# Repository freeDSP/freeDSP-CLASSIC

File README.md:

# freeDSP CLASSIC

BOARD STATUS: READY TO BE BUILT

MAIN COORDINATOR: [sudlud](https://github.com/sudlud)

The freeDSP CLASSIC is a cost-effective real-time audio signal processing solution for researchers and the do-it-yourself community. It is a bare circuit board that can be incorporated into your own projects. It comes with no housing. Easy assembling and simple programmability are the main focus. It is based on Analog Devices’ ADAU1701 DSP chip together with the free graphical development environment SigmaStudio. The programming model is function-block based – comparable to other graphical programming languages like PureData or Max/MSP. Many prebuilt blocks (e.g., filters, compressors, effects, or logic) can be placed in the signal path via drag and drop. If the included libraries do not have the functions needed, low-level blocks, such as multipliers and delays, can be wired together to create custom algorithms.

This board uses MAINLY THT components. The trickiest part is soldering the DSP, which comes in an SMD packaging. A complete SMD version is under development.

## Features

The freeDSP CLASSIC board offers two analog inputs and four analog outputs. Compared to other DSP solutions with easy programmability, the freeDSP and SigmaStudio offer a much wider range of DSP processing options and interface controls. It can be used in various audio applications, e.g.:

* Room compensation / system equalization
* Digital crossovers in active loudspeaker concepts
* Multiband dynamics processing
* Delay compensation / phase shift
* Bass enhancement
* Subwoofer integration
* Advanced instrument audio effect units
* Stereo image widening
…

For more information, please refer to the website www.freeDSP.cc and the documentation.  

## License

This work and all other materials under https://github.com/freeDSP are licensed under a <a rel="license" href="http://creativecommons.org/licenses/by-sa/4.0/legalcode">Creative Commons Attribution Share-Alike 4.0 license</a>. This allows for both personal and commercial derivative works, as long as they credit freeDSP and release their designs under the same license.

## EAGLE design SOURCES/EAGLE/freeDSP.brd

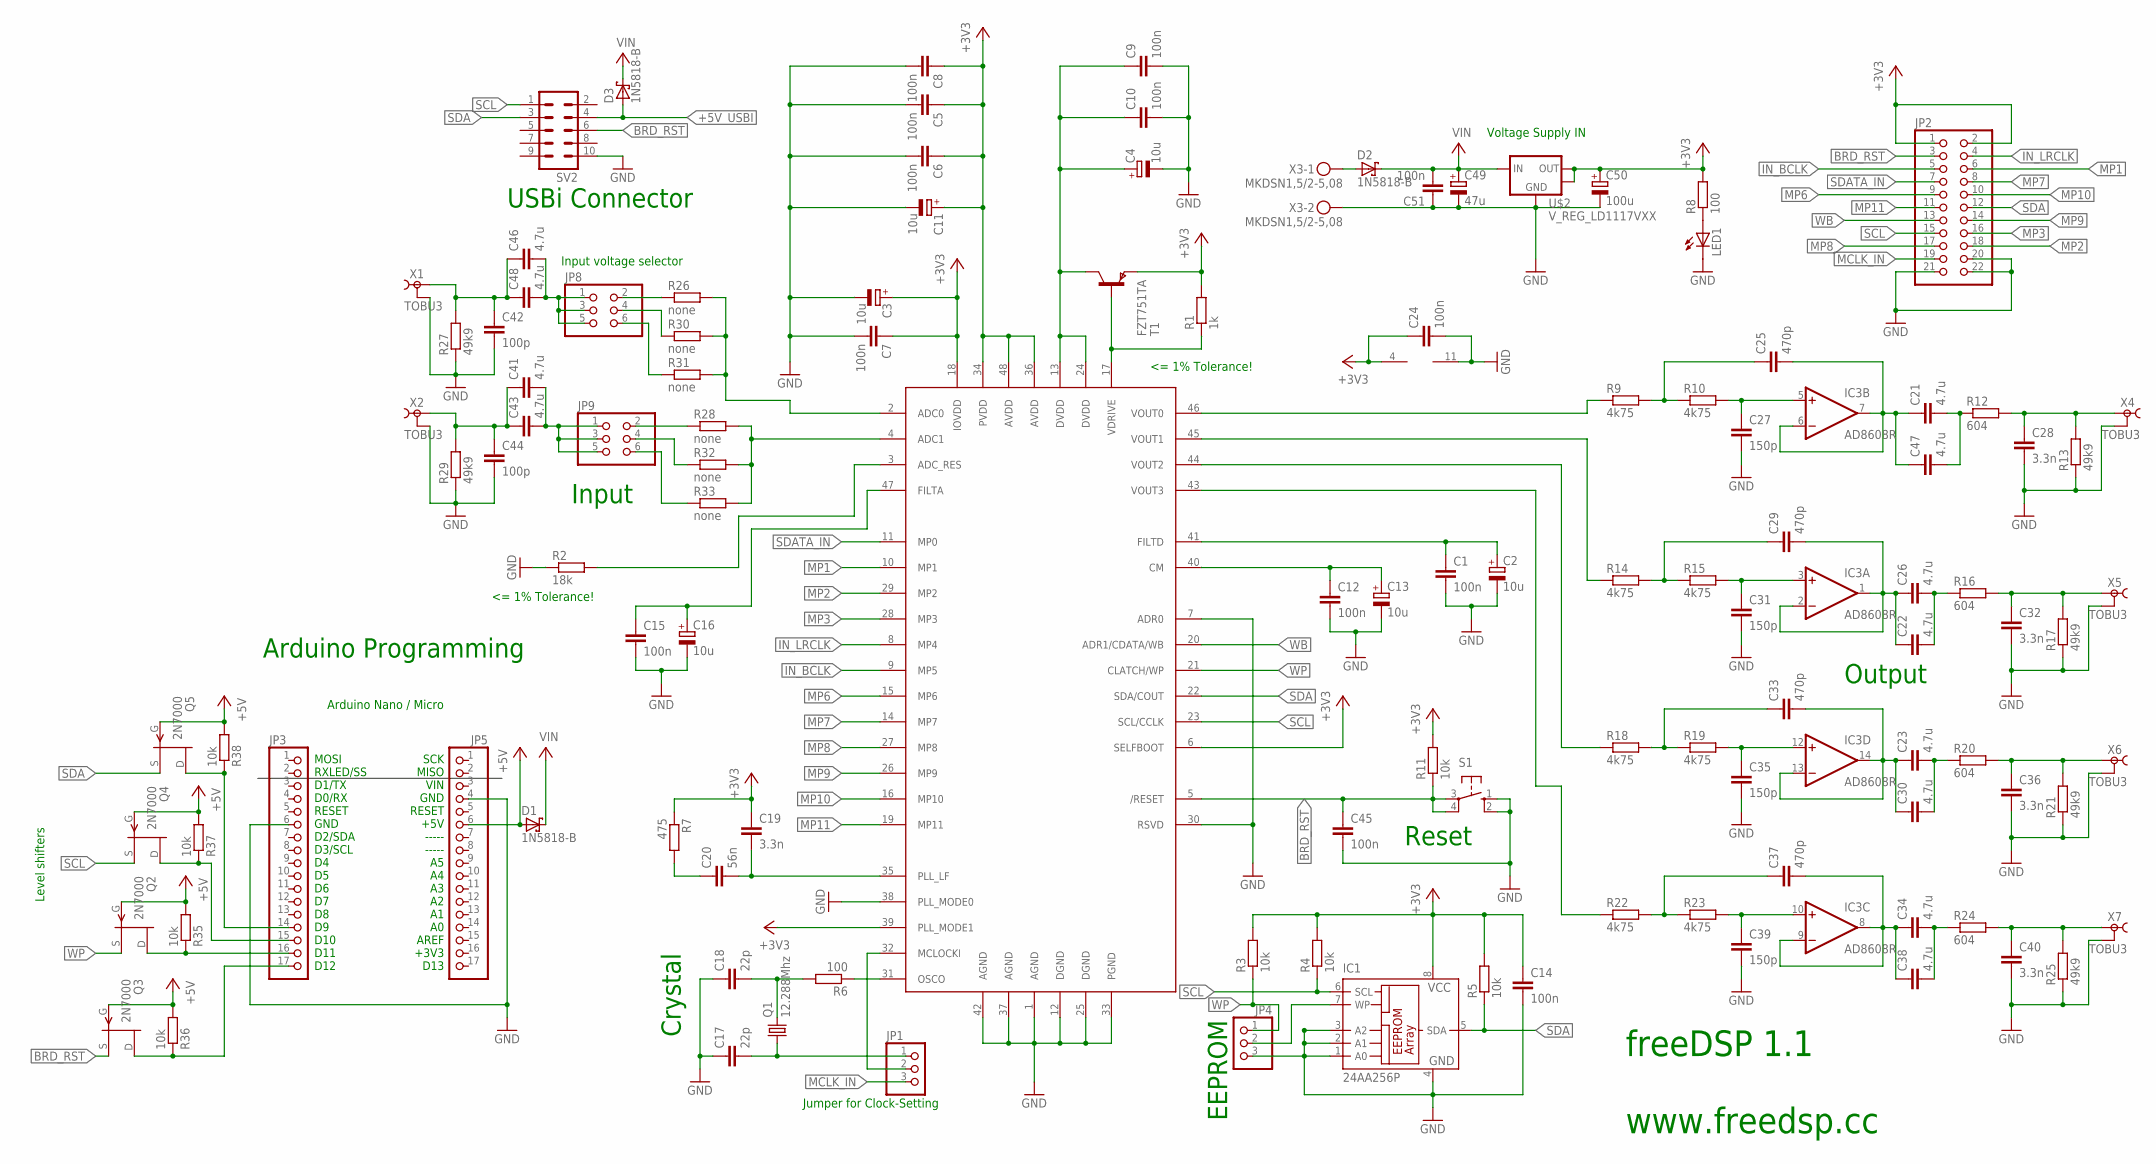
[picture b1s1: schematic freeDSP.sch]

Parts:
C1, C5, C6, C7, C8, C9, C10, C12, C14, C15, C24, C45, C51: 100n; C025-025X050
C2, C3, C4, C11, C13, C16: 10u; E1,8-4
C17, C18: 22p; C025-025X050
C19, C28, C32, C36, C40: 3.3n; C025-025X050
C20: 56n; C025-025X050
C21, C22, C23, C26, C30, C34, C38, C41, C43, C46, C47, C48: 4.7u; C050-075X075
C25, C29, C33, C37: 470p; C050-050X075
C27, C31, C35, C39: 150p; C025-025X050
C42, C44: 100p; C025-025X050
C49: 47u; E2,5-6
C50: 100u; E2,5-6
D1, D2, D3: 1N5818-B; DO41-7.6
IC1: 24AA256P; DIL8
IC3: AD8608R; SO-14
JP1, JP4: PINHD-1X3; 1X03
JP2: PINHD-2X11; 2X11
JP3, JP5: PINHD-1X17; 1X17
JP8, JP9: PINHD-2X3; 2X03
LED1: LED3MM
Q1: 12.288Mhz; HC49/S
Q2, Q3, Q4, Q5: 2N7000; TO92
R1: 1k; 0207/10
R2: 18k; 0207/10
R3, R4, R5, R11, R35, R36, R37, R38: 10k; 0207/10
R6, R8: 100; 0207/10
R7: 475; 0207/10
R9, R10, R14, R15, R18, R19, R22, R23: 4k75; 0207/10
R12, R16, R20, R24: 604; 0207/10
R13, R17, R21, R25, R27, R29: 49k9; 0207/10
R26, R28, R30, R31, R32, R33: none; 0207/10
S1: 10-XX; B3F-10XX
SV2: ML10
T1: FZT751TA; SOT223
U$1: ADAU1701; LQFP-48
U$2: V_REG_LD1117VXX; 78XXL
X1, X2, X4, X5, X6, X7: TOBU3
X3: MKDSN1,5/2-5,08

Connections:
1V8: C4.+, C9.1, C10.1, T1.2 (C), T1.4 (C), U$1.13 (DVDD), U$1.24 (DVDD)
+3V3: C3.+, C5.1, C6.1, C7.1, C8.1, C11.+, C14.1, C19.1, C24.1, C50.+, IC1.8 (VCC), IC3.4 (V+), JP2.1, JP2.2, R1.2, R3.2, R4.2, R5.2, R7.1, R8.2, R11.2, T1.3 (E), U$1.6 (SELFBOOT), U$1.18 (IOVDD), U$1.34 (PVDD), U$1.36 (AVDD), U$1.39 (PLL_MODE1), U$1.48 (AVDD), U$2.GND (OUT), U$2.OUT2
+5V: D1.A, JP5.6, Q2.2 (G), Q3.2 (G), Q4.2 (G), Q5.2 (G), R35.2, R36.2, R37.2, R38.2
+5V_USBI: D3.A, SV2.4
ADC0: R28.2, R32.2, R33.2, U$1.4 (ADC1)
BRD_RST: C45.1, JP2.3, Q3.3 (S), R11.1, S1.3, S1.4 (P1), SV2.6, U$1.5 (/RESET)
CM: C12.1, C13.+, U$1.40 (CM)
FILTA: C15.1, C16.+, U$1.47 (FILTA)
FILTD: C1.1, C2.+, U$1.41 (FILTD)
FILTOUT0: C28.1, R12.2, R13.2, X4.1
FILTOUT1: C32.1, R16.2, R17.2, X5.1
FILTOUT2: C36.1, R20.2, R21.2, X6.1
FILTOUT3: C40.1, R24.2, R25.2, X7.1
GND: C1.2, C2.-, C3.-, C4.-, C5.2, C6.2, C7.2, C8.2, C9.2, C10.2, C11.-, C12.2, C13.-, C14.2, C15.2, C16.-, C17.1, C18.1, C24.2, C27.2, C28.2, C31.2, C32.2, C35.2, C36.2, C39.2, C40.2, C42.2, C44.2, C45.2, C49.-, C50.-, C51.1, IC1.1 (A0), IC1.2 (A1), IC1.3 (A2), IC1.4 (GND), IC3.11 (V-), JP2.20, JP2.21, JP2.22, JP3.6, JP4.3, JP5.4, LED1.K (C), R2.1, R13.1, R17.1, R21.1, R25.1, R27.1, R29.1, S1.1 (S), S1.2 (S1), SV2.10, U$1.1 (AGND), U$1.7 (ADR0), U$1.12 (DGND), U$1.25 (DGND), U$1.30 (RSVD), U$1.33 (PGND), U$1.37 (AGND), U$1.38 (PLL_MODE0), U$1.42 (AGND), U$2.IN (GND), X1.2, X1.2@1 (2), X1.2@2 (2), X2.2, X2.2@1 (2), X2.2@2 (2), X3.2, X4.2, X4.2@1 (2), X4.2@2 (2), X5.2, X5.2@1 (2), X5.2@2 (2), X6.2, X6.2@1 (2), X6.2@2 (2), X7.2, X7.2@1 (2), X7.2@2 (2)
IN_BCLK: JP2.5, U$1.9 (MP5)
IN_LRCLK: JP2.4, U$1.8 (MP4)
MCLK_IN: JP1.3, JP2.19
MP1: JP2.6, U$1.10 (MP1)
MP2: JP2.18, U$1.29 (MP2)
MP3: JP2.16, U$1.28 (MP3)
MP6: JP2.9, U$1.15 (MP6)
MP7: JP2.8, U$1.14 (MP7)
MP8: JP2.17, U$1.27 (MP8)
MP9: JP2.14, U$1.26 (MP9)
MP10: JP2.10, U$1.16 (MP10)
MP11: JP2.11, U$1.19 (MP11)
unnamed: R2.2, U$1.3 (ADC_RES)
unnamed: R1.1, T1.1 (B), U$1.17 (VDRIVE)
unnamed: C19.2, C20.2, U$1.35 (PLL_LF)
unnamed: C23.1, C30.1, C33.2, IC3.13 (-IN), IC3.14 (OUT)
unnamed: C20.1, R7.2
unnamed: C18.2, Q1.2, R6.2
unnamed: C17.2, JP1.1, Q1.1
unnamed: R6.1, U$1.31 (OSCO)
unnamed: LED1.A, R8.1
unnamed: JP1.2, U$1.32 (MCLOCKI)
unnamed: JP3.15, Q4.1 (D), R37.1
unnamed: C21.2, C47.2, R12.1
unnamed: C29.1, R14.2, R15.1
unnamed: JP3.14, Q5.1 (D), R38.1
unnamed: C22.1, C26.1, C29.2, IC3.1 (OUT), IC3.2 (-IN)
unnamed: C31.1, IC3.3 (+IN), R15.2
unnamed: C25.1, R9.2, R10.1
unnamed: C21.1, C25.2, C47.1, IC3.6 (-IN), IC3.7 (OUT)
unnamed: C22.2, C26.2, R16.1
unnamed: C27.1, IC3.5 (+IN), R10.2
unnamed: C33.1, R18.2, R19.1
unnamed: C23.2, C30.2, R20.1
unnamed: JP3.16, Q2.1 (D), R35.1
unnamed: C35.1, IC3.12 (+IN), R19.2
unnamed: JP3.17, Q3.1 (D), R36.1
unnamed: C37.1, R22.2, R23.1
unnamed: C34.1, C37.2, C38.1, IC3.8 (OUT), IC3.9 (-IN)
unnamed: C39.1, IC3.10 (+IN), R23.2
unnamed: C34.2, C38.2, R24.1
unnamed: C46.2, C48.2, JP8.1, JP8.3, JP8.5
unnamed: C42.1, C46.1, C48.1, R27.2, X1.1
unnamed: JP8.2, R26.1
unnamed: JP8.4, R30.1
unnamed: C41.1, C43.1, C44.1, R29.2, X2.1
unnamed: JP8.6, R31.1
unnamed: C41.2, C43.2, JP9.1, JP9.3, JP9.5
unnamed: JP9.2, R28.1
unnamed: JP9.4, R32.1
unnamed: JP9.6, R33.1
unnamed: R26.2, R30.2, R31.2, U$1.2 (ADC0)
unnamed: D2.A, X3.1
unnamed: IC1.7 (WP), JP4.2
SCL: IC1.6 (SCL), JP2.15, Q4.3 (S), R4.1, SV2.1, U$1.23 (SCL/CCLK)
SDA: IC1.5 (SDA), JP2.12, Q5.3 (S), R5.1, SV2.3, U$1.22 (SDA/COUT)
SDATA_IN: JP2.7, U$1.11 (MP0)
V+: C49.+, C51.2, D1.C, D2.C, D3.C, U$2.OUT (IN)
VOUT0: R9.1, U$1.46 (VOUT0)
VOUT1: R14.1, U$1.45 (VOUT1)
VOUT2: R18.1, U$1.44 (VOUT2)
VOUT3: R22.1, U$1.43 (VOUT3)
WB: JP2.13, U$1.20 (ADR1/CDATA/WB)
WP: JP4.1, Q2.3 (S), R3.1, U$1.21 (CLATCH/WP)

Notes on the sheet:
<= 1% Tolerance!
EEPROM
Jumper for Clock-Setting
Crystal
Reset
Output
Input
Input voltage selector
USBi Connector
Arduino Programming
Voltage Supply IN
Arduino Nano / Micro
MOSI RXLED/SS D1/TX D0/RX RESET GND D2/SDA D3/SCL D4 D5 D6 D7 D8 D9 D10 D11 D12
SCK MISO VIN GND RESET +5V ----- ----- A5 A4 A3 A2 A1 A0 AREF +3V3 D13
Level shifters
freeDSP 1.1 www.freedsp.cc

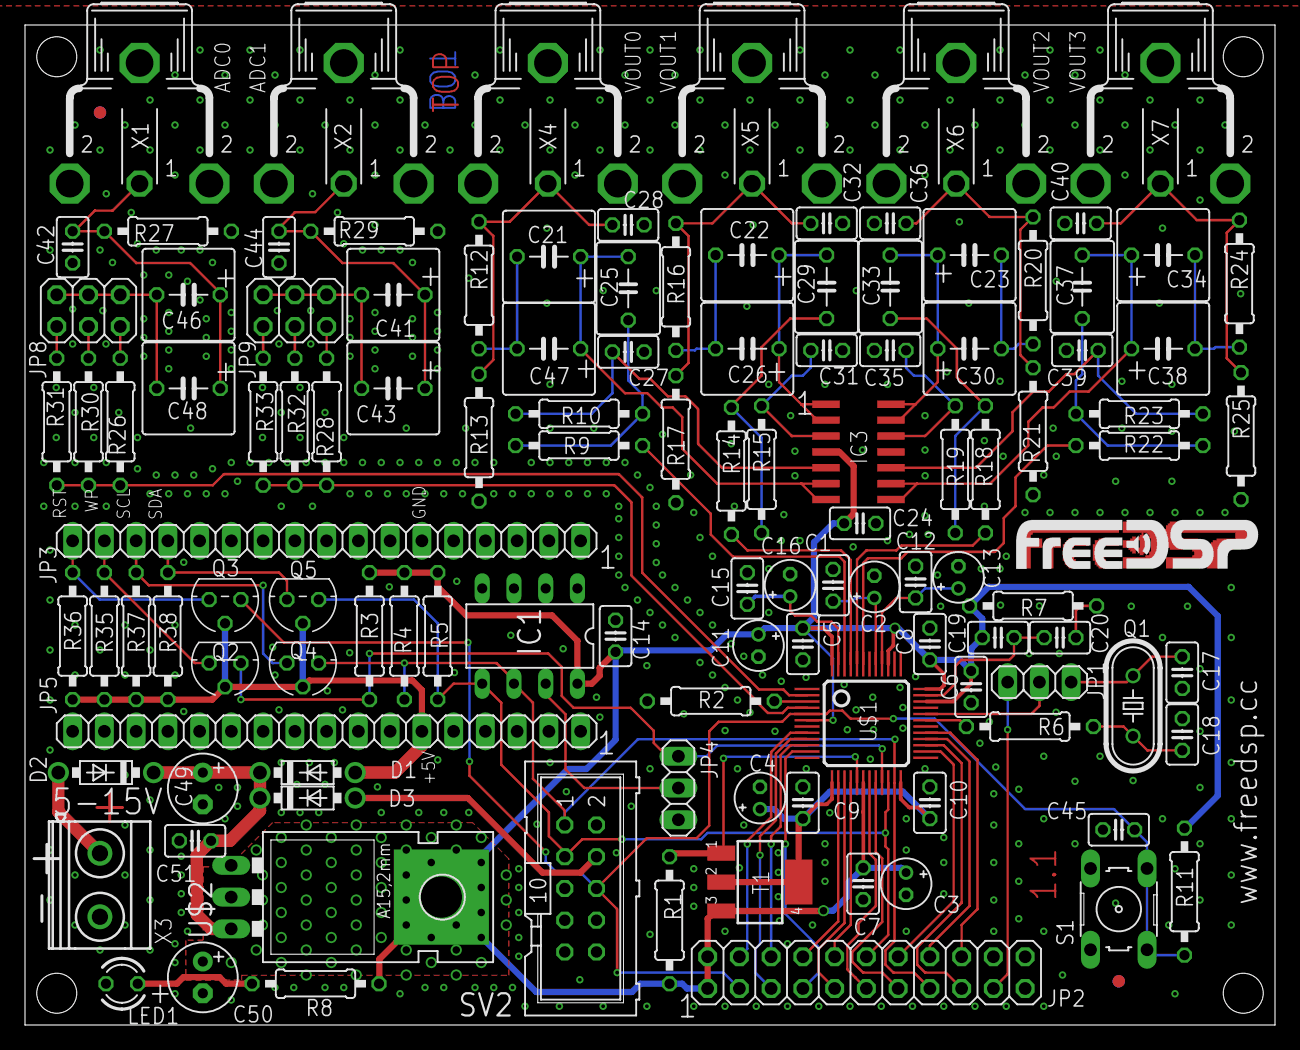
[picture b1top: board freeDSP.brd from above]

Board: 2 copper layers, 100.0 x 80.0 mm, 120 parts (0 on the bottom side), 78 nets.

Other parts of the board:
U$3, U$4: VISION_REF10

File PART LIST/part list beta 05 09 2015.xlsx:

Part list |  |  |  | reichelt.de
Part | Description | Label | Qty. | Order number
C1, C5, C6, C7, C8, C9, C10, C12, C14, C15, C24, C45, C51 | Ceramic capacitor, 100nF | 104 | 13 | X7R-2,5 100N
C2, C3, C4, C11, C13, C16 | Electrolytic capacitor, radial, 10µF, 16V/50V | 10µF/16 | 6 | SM 10/16 RAD
C17, C18 | Ceramic capacitor, 22pF, 63V/200V | 22/100V | 2 | KERKO 22P
C19, C28, C32, C36, C40 | Ceramic capacitor, 3.3nF, 63V/50V | 332 | 5 | KERKO 3,3N
C20 | Ceramic capacitor, 56nF, 100V | green blue orange | 1 | not available
C21, C22, C23, C26, C30, C34, C38, C41, C43, C46, C47, C48 | Foil capacitor, 4.7µF | 4,7µF | 12 | MKS-2 4,7µ
C25, C29, C33, C37 | Ceramic capacitor, 470pF, 500V | 470 | 4 | KERKO-500 470P
C27, C31, C35, C39 | Ceramic capacitor, 150pF, 63V | 151 | 4 | KERKO 150P
C42, C44 | Ceramic capacitor, 100pF, 50V | 101 | 2 | KERKO 100P
C49 | Electrolytic capacitor, radial, 47µF, 35V | 47µF/35 | 1 | RAD 47/35
C50 | Electrolytic capacitor, radial, 100µF, 6.3V | 100µF/16 | 1 | RAD FC 100/16
D1, D2, D3 | Shottky diode, 1N5818, DO41, 30V, 1A | 1N5818 | 3 | 1N 5818
IC1a | EEPROM, serial, 256kBit, DIP-8 | 24AA256 | 1 | 24AA256-I/P
IC1b | IC socket, DIP8 (for EEPROM) | - | 1 | GS 8
IC3 | AD8608 | AD8608 | 1 | Order via DigiKey
JP1, JP4 | Multi-pin connector, 1x3, RM 2.54mm | - | 2 | MPE 087-1-003
JP2 | Multi-pin connector, 2x13, RM 2.54mm, needs to be shortened to 2x11 | - | 1 | SL 2x13G 2,54
JP3, JP5 | Plug connector, 1x20, RM 2.54mm, needs to be shortened to 1x17 | - | 2 | BL 1x20G8 2,54
JP8, JP9 | Multi-pin connector, 2x3, RM 2.54mm | - | 2 | MPE 087-2-006
LED1 | LED, 3mm, green | - | 1 | LED 3MM 2MA GN
Q1 | Quartz crystal, 12.288Mhz, HC49/U-S | - | 1 | 12,2880-HC49U-S
Q2, Q3, Q4, Q5 | n-MOSFET 2N7000 | - | 4 | 2N 7000
R1 | Resistor, 1kΩ | brown black black brown brown | 1 | METALL 1,00K
R2, R26, R28 | Resistor, 18kΩ | brown grey black red brown | 3 | METALL 18,0K
R3, R4, R5, R11, R35, R36, R37, R38 | Resistor, 10kΩ | brown black black red brown | 8 | METALL 10,0K
R6, R8 | Resistor, 100Ω | brown black black black brown | 2 | METALL 100
R7 | Resistor, 475Ω | yellow violet green black brown | 1 | METALL 475
R9, R10, R14, R15, R18, R19, R22, R23 | Resistor, 4.75kΩ | yellow violet green brown brown | 8 | METALL 4,75k
R12, R16, R20, R24 | Resistor, 604Ω | blue black yellow black brown | 4 | METALL 604
R13, R17, R21, R25, R27, R29 | Resistor, 49.9kΩ | yellow white white red brown | 6 | METALL 49,9K
R31, R33 | Resistor, 7.15kΩ | violet brown green brown brown | 2 | METALL 7,15K
R30, R32 | Resistor, 10.5kΩ | brown black green red brown | 2 | METALL 10,5K
S1 | Switch, 6x6mm, H: 4.3mm; 12V | - | 1 | TASTER 3301
SV2 | Boxed header, 10 pins | - | 1 | WSL 10G
T1 | Zetex PNP transistor | - | 1 | FZT 751TA
U1 | ADAU1701 | - | 1 | Order via DigiKey
U2 | LM1117 +3V3 voltage regulator | - | 1 | LM 1117 T3,3
X1, X2, X4, X5, X6, X7 | Cinch connector | - | 6 | CBP-G
JP1, JP4, JP8, JP9 | Jumper | - | 4 | JUMPER 2,54 BL
X3 | Terminal, 2x, 5.08mm grid | - | 1 | AKL 101-02

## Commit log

2015-12-21 folder structure + initial sources V1.1
    added folder structure + initial sources V1.1
2016-03-04 Added Link to documentation
2016-10-08 Add licensing info to schematic & add PNG-Schematic
    This enables users to view the schematic without
    the need to download & install EAGLE on their
    computer.
2016-12-29 Update ADAU1701 datasheet to Rev. C
    Datasheet retrieved from:
    http://www.analog.com/media/en/technical-documentation/data-sheets/ADAU1701.pdf

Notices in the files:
parts and their libraries:
SparkFun-PowerIC: Licensing: Creative Commons ShareAlike 4.0 International - https://creativecommons.org/licenses/by-sa/4.0
dicons: Copyright (C) 2004, Bob Starr (rtzaudio@mindspring.com)
